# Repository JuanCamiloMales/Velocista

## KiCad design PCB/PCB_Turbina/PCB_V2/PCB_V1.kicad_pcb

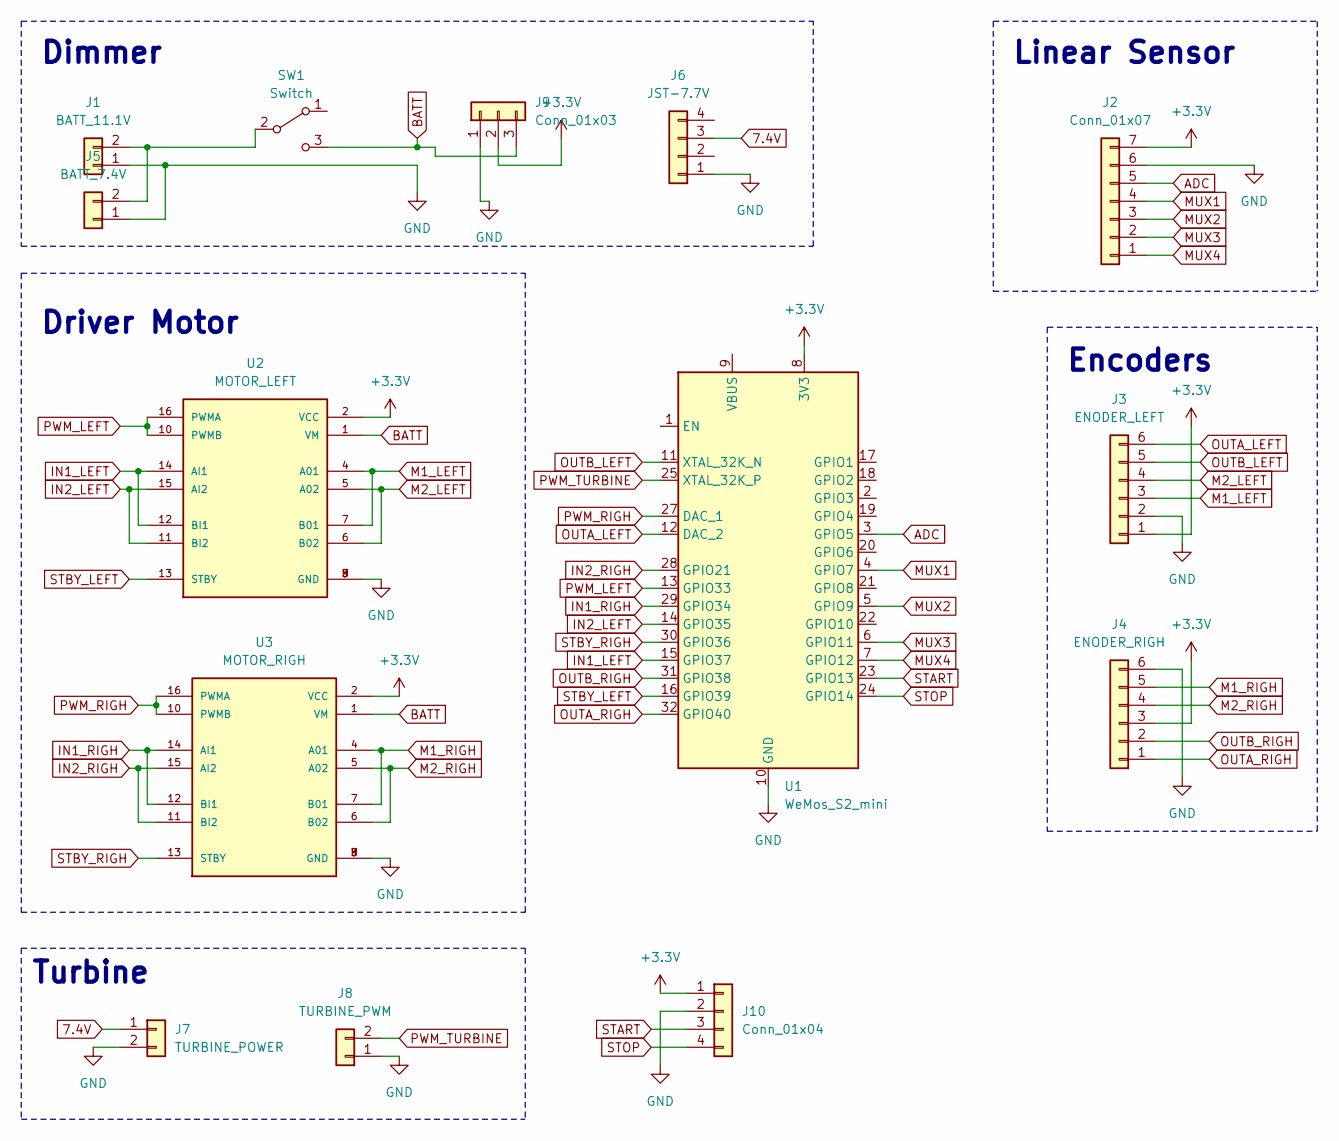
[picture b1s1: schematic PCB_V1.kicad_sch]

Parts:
J1: BATT_11.1V; AMASS_XT30U-F_1x02_P5.0mm_Vertical
J2: Conn_01x07; PinHeader_1x07_P2.54mm_Vertical
J3: ENODER_LEFT; PinHeader_1x06_P2.54mm_Vertical
J4: ENODER_RIGH; PinHeader_1x06_P2.54mm_Vertical
J5: BATT_7.4V; JST_XH_B2B-XH-A_1x02_P2.50mm_Vertical
J6: JST-7.7V; JST_XH_B4B-XH-A_1x04_P2.50mm_Vertical
J7: TURBINE_POWER; JST_XH_B2B-XH-A_1x02_P2.50mm_Vertical
J8: TURBINE_PWM; JST_XH_B2B-XH-A_1x02_P2.50mm_Vertical
J9: Conn_01x03; PinHeader_1x03_P2.54mm_Vertical
J10: Conn_01x04; PinHeader_1x04_P2.54mm_Vertical
SW1: Switch; PinHeader_1x03_P2.54mm_Vertical
U1: WeMos_S2_mini; WEMOS_S2_mini
U2: MOTOR_LEFT; TB6612FNG_MODULE; PARTREV 11-13-17
U3: MOTOR_RIGH; TB6612FNG_MODULE; PARTREV 11-13-17

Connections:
7.4V: J6.3, J7.1
+3.3V: J2.7, J3.1, J4.3, J9.2, J10.1, U1.8 (3V3), U2.2 (VCC), U3.2 (VCC)
ADC: J2.5, U1.3 (GPIO5)
BATT: J9.3, SW1.3 (C), U2.1 (VM), U3.1 (VM)
GND: J1.1, J2.6, J3.2, J4.6, J5.1, J6.1, J7.2, J8.1, J9.1, J10.2, U1.10 (GND), U1.26 (GND), U2.3 (GND), U2.8 (GND), U2.9 (GND), U3.3 (GND), U3.8 (GND), U3.9 (GND)
IN1_LEFT: U1.15 (GPIO37), U2.12 (BI1), U2.14 (AI1)
IN1_RIGH: U1.29 (GPIO34), U3.12 (BI1), U3.14 (AI1)
IN2_LEFT: U1.14 (GPIO35), U2.11 (BI2), U2.15 (AI2)
IN2_RIGH: U1.28 (GPIO21), U3.11 (BI2), U3.15 (AI2)
M1_LEFT: J3.3, U2.4 (A01), U2.7 (B01)
M1_RIGH: J4.5, U3.4 (A01), U3.7 (B01)
M2_LEFT: J3.4, U2.5 (A02), U2.6 (B02)
M2_RIGH: J4.4, U3.5 (A02), U3.6 (B02)
MUX1: J2.4, U1.4 (GPIO7)
MUX2: J2.3, U1.5 (GPIO9)
MUX3: J2.2, U1.6 (GPIO11)
MUX4: J2.1, U1.7 (GPIO12)
unnamed: J1.2, J5.2, SW1.2 (B)
OUTA_LEFT: J3.6, U1.12 (DAC_2)
OUTA_RIGH: J4.1, U1.32 (GPIO40)
OUTB_LEFT: J3.5, U1.11 (XTAL_32K_N)
OUTB_RIGH: J4.2, U1.31 (GPIO38)
PWM_LEFT: U1.13 (GPIO33), U2.10 (PWMB), U2.16 (PWMA)
PWM_RIGH: U1.27 (DAC_1), U3.10 (PWMB), U3.16 (PWMA)
PWM_TURBINE: J8.2, U1.25 (XTAL_32K_P)
START: J10.3, U1.23 (GPIO13)
STBY_LEFT: U1.16 (GPIO39), U2.13 (STBY)
STBY_RIGH: U1.30 (GPIO36), U3.13 (STBY)
STOP: J10.4, U1.24 (GPIO14)

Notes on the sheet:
Encoders
Driver Motor
Turbine
Linear Sensor
Dimmer

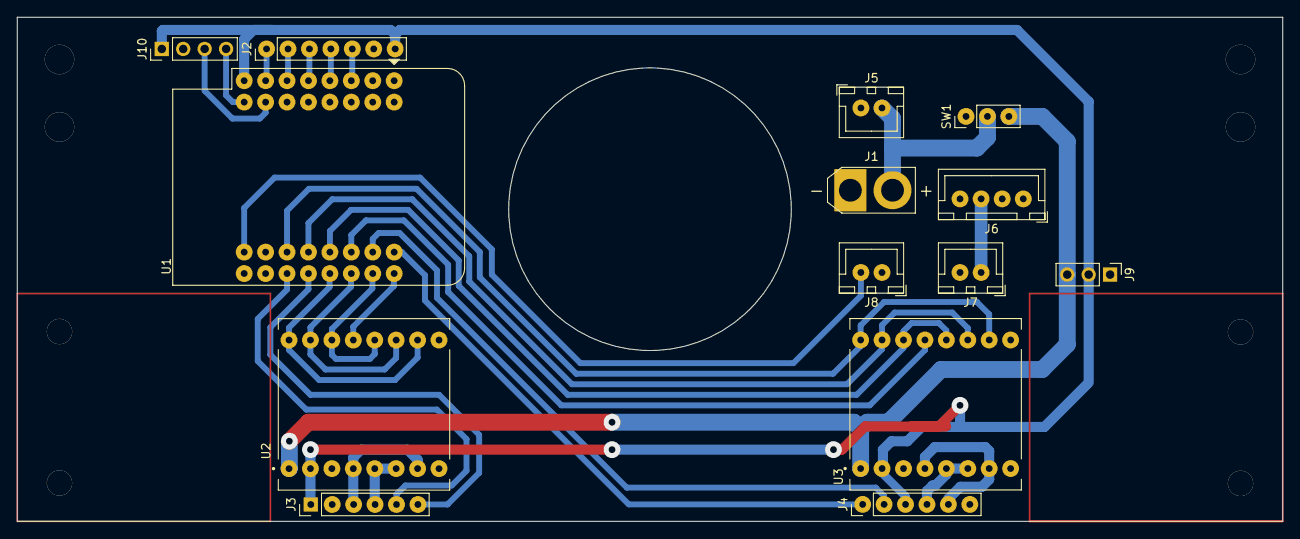
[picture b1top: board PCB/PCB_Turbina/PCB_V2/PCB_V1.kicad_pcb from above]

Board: 2 copper layers, 150.0 x 59.8 mm, 14 parts (0 on the bottom side), 29 nets.

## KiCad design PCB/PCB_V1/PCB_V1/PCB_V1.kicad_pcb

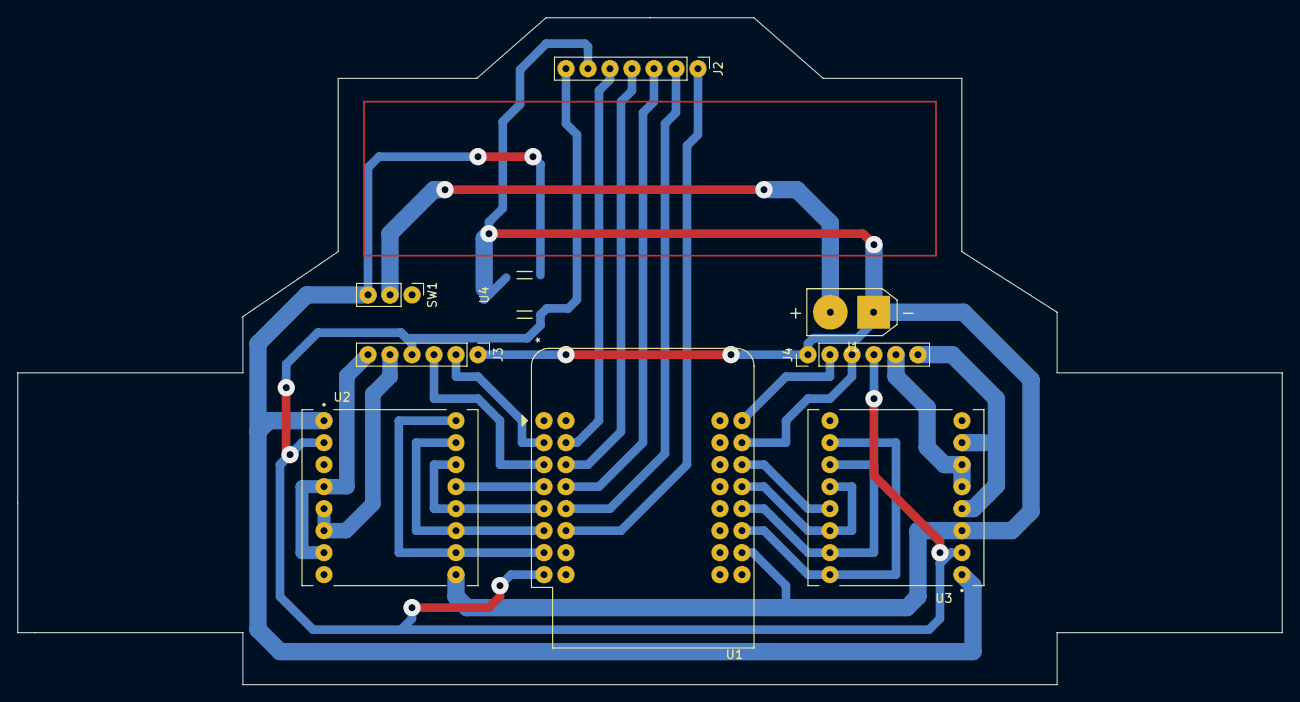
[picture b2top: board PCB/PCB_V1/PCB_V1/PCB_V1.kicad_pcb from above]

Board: 2 copper layers, 146.0 x 77.0 mm, 9 parts (0 on the bottom side), 25 nets.

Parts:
J1: BATT; AMASS_XT30U-F_1x02_P5.0mm_Vertical
J2: Conn_01x07; PinHeader_1x07_P2.54mm_Vertical
J3: ENODER_LEFT; PinHeader_1x06_P2.54mm_Vertical
J4: ENODER_RIGH; PinHeader_1x06_P2.54mm_Vertical
SW1: Switch; PinHeader_1x03_P2.54mm_Vertical
U1: WeMos_S2_mini; WEMOS_S2_mini
U2: MOTOR_LEFT; TB6612FNG_MODULE
U3: MOTOR_RIGH; TB6612FNG_MODULE
U4: LP38690DT-3.3/NOPB; LP38690

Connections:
+3.3V: J2.7, J3.4, J4.4, U1.8 (3V3), U2.2 (VCC), U3.2 (VCC), U4.1 (Vout)
ADC: J2.5, U1.18 (GPIO2)
BATT: SW1.3 (C), U2.1 (VM), U3.1 (VM), U4.3 (Vin)
GND: J1.1, J2.6, J3.1, J4.1, U1.10 (GND), U1.26 (GND), U2.3 (GND), U2.8 (GND), U2.9 (GND), U3.3 (GND), U3.8 (GND), U3.9 (GND), U4.2 (GND)
IN1_LEFT: U1.5 (GPIO9), U2.12 (BI1), U2.14 (AI1)
IN1_RIGH: U1.13 (GPIO33), U3.12 (BI1), U3.14 (AI1)
IN2_LEFT: U1.6 (GPIO11), U2.11 (BI2), U2.15 (AI2)
IN2_RIGH: U1.12 (DAC_2), U3.11 (BI2), U3.15 (AI2)
M1_LEFT: J3.6, U2.4 (A01), U2.7 (B01)
M1_RIGH: J4.6, U3.4 (A01), U3.7 (B01)
M2_LEFT: J3.5, U2.5 (A02), U2.6 (B02)
M2_RIGH: J4.5, U3.5 (A02), U3.6 (B02)
MUX1: J2.4, U1.19 (GPIO4)
MUX2: J2.3, U1.20 (GPIO6)
MUX3: J2.2, U1.21 (GPIO8)
MUX4: J2.1, U1.22 (GPIO10)
unnamed: J1.2, SW1.2 (B)
OUTA_LEFT: J3.3, U1.3 (GPIO5)
OUTA_RIGH: J4.3, U1.15 (GPIO37)
OUTB_LEFT: J3.2, U1.2 (GPIO3)
OUTB_RIGH: J4.2, U1.16 (GPIO39)
PWM_LEFT: U1.7 (GPIO12), U2.10 (PWMB), U2.16 (PWMA)
PWM_RIGH: U1.11 (XTAL_32K_N), U3.10 (PWMB), U3.16 (PWMA)
STBY_LEFT: U1.4 (GPIO7), U2.13 (STBY)
STBY_RIGH: U1.14 (GPIO35), U3.13 (STBY)

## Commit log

2023-11-14 Correccion V1
2023-11-18 Correccion Agujeros 3mm
2023-11-30 Correccion modulo arranque PCB
2023-12-01 PCB_V3
2024-02-16 Servidor WIFI para cambiar constantes PID
    Crea una red wifi donde se pueden ingresar a una pagina para cambiar las constantes PID
2024-02-21 Codigos de prueba individuales
    Codigo sensores, motores, turbina
2024-02-21 Integracion 21/02/2024
